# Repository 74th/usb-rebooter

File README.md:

# Adapter to turn USB power on/off once every 12 hours

12 時間後とに USB 電源をオン/オフするためのアダプタ

## features

- turn USB power on/off once every 12 hours
- using CH217 for switching
- using CH32V003 for timer
- count down shown by UART

### Japanese

- 12 時間ごとに USB 電源をオン/オフする
- CH217 を使用して電源を切り替える
- CH32V003 を使用してタイマーを実装する
- UART でカウントダウンを表示する

## Documents

- semantics: [PDF](./documents/usb_rebooter-semantics-v1.0.0.pdf), [kicanvas](https://kicanvas.org/?github=https%3A%2F%2Fgithub.com%2F74th%2Fusb-rebooter%2Fblob%2Fv1.0.0%2Fpcb%2Fusb_auto_reboot.kicad_sch)
- pcb: [kicanvas](https://kicanvas.org/?github=https%3A%2F%2Fgithub.com%2F74th%2Fusb-rebooter%2Fblob%2Fv1.0.0%2Fpcb%2Fusb_auto_reboot.kicad_pcb)

## parts list

### v1.0.0

| Designator | Quantity | Designation                                   |
| ---------- | -------- | --------------------------------------------- |
| J1         | 1        | USB Type-C Mid-mount Socket Molex 216990-0002 |
| J2         | 1        | USB Type-C Plug 00402-UCAM002-X               |
| R1         | 1        | 0805 Register 56k                             |
| R2         | 1        | 0805 Register 10k                             |
| C1         | 1        | 0805 Capacitor 100n                           |
| C2         | 1        | 0805 Capacitor 10u                            |
| D1         | 1        | 0805 LED BLUE                                 |
| U1         | 1        | WCH CH217K                                    |
| U2         | 1        | WCH CH32V003J4M6                              |
| CH1        | 1        | SWD 1Wire TH                                  |
| CH2        | 1        | UART_TX TH                                    |

## License

MIT

We would appreciate it if you would not sell them. 販売はしないでいただけるとありがたいです。

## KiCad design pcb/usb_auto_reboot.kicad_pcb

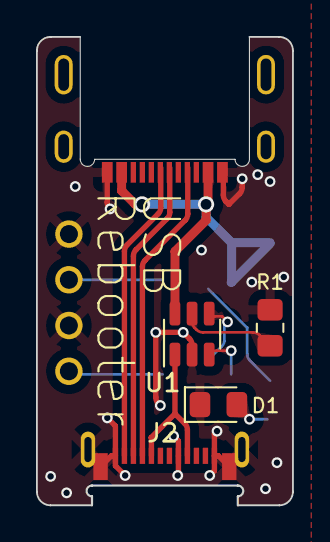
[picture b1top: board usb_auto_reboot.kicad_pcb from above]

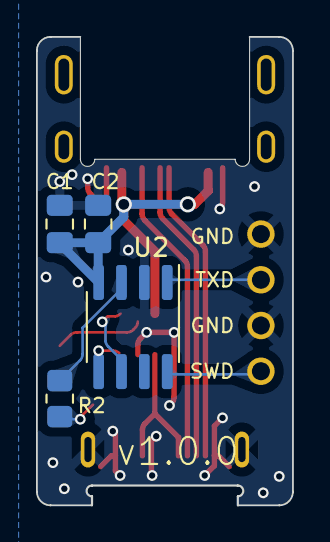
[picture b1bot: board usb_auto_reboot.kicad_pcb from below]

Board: 2 copper layers, 14.2 x 26.0 mm, 11 parts (5 on the bottom side), 13 nets.

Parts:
C1: 100n; Capacitor_0805_2012
C2: 10u; Capacitor_0805_2012
CH1: SWD 1Wire; 2Pin
CH2: UART_TX; 2Pin
D1: BLUE; LED_0805_2012Metric_Pad1.15x1.40mm_HandSolder
J1: USB2.0 C 12Pin Receptable; USB-C-12-Pin-MidMount-ali-v5-12Pin
J2: USB3.0 C Plug; USB-C-MALE-00402-UCAM002-X
R1: 56k; Register_0805_2012
R2: 10k; Register_0805_2012
U1: CH217K; SOT-23-6
U2: CH32V003J4M6; SOIC-8_3.9x4.9mm_P1.27mm

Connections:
+5V: C1.1, C2.1, J1.2 (VBUS_A4/B9), J1.11 (VBUS_B4/A9), U1.6 (VIN), U2.4 (VDD)
/CC: J1.4 (CC1_A5), J2.A5 (CC_A5)
/D+: J1.6 (D+_A6), J2.A6 (D+_A6)
/D-: J1.7 (D-_A7), J2.A7 (D-_A7)
/EN: U1.4 (EN#), U2.6 (PC2)
/FLAG: U1.3 (FLAG#), U2.5 (PC1)
/LED: R2.1, U2.3 (PA2)
GND: C1.2, C2.2, CH1.2 (GND), CH2.2 (GND), D1.1 (K), J1.1 (GND_A1/B12), J1.12 (GND_A12/B1), J2.1 (SHIELD_GND), J2.A1 (GND_A1), J2.A12 (GND_A12), J2.B12 (GND_B12), R1.2, U1.2 (GND), U2.2 (GND)
unnamed: CH1.1 (SWDIO), U2.8 (PD4/PD5/PD1/SWIO)
unnamed: CH2.1 (TXD), U2.1 (PD6/PA1)
unnamed: D1.2 (A), R2.2
unnamed: R1.1, U1.5 (ISET)
VCC: J2.A4 (VBUS_A4), J2.B9 (VBUS_B9), U1.1 (VOUT)

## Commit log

2023-08-12 first
2023-08-12 work
2023-08-12 uart afio
2023-08-16 fix name
2023-08-16 fix README.md
